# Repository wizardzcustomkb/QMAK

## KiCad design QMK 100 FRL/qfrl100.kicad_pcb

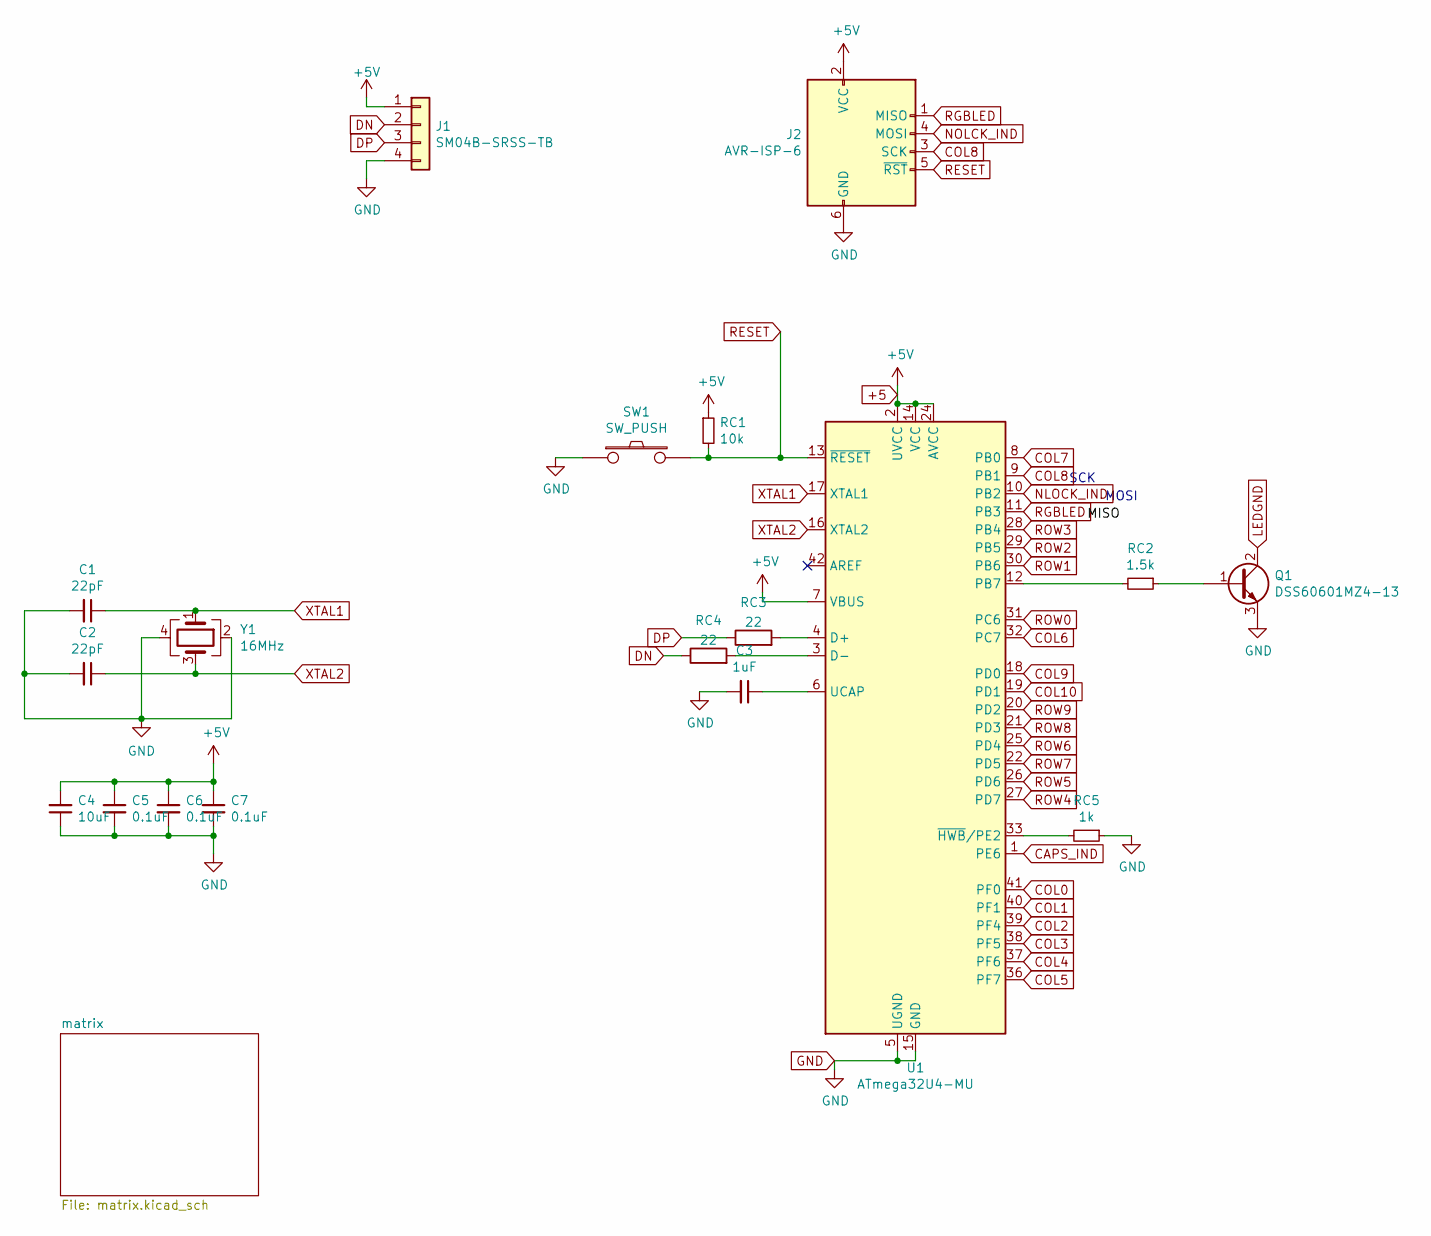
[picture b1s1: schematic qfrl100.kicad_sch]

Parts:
C1, C2: 22pF; C_0603_1608Metric
C3: 1uF; C_0603_1608Metric
C4: 10uF; C_0603_1608Metric
C5, C6, C7: 0.1uF; C_0603_1608Metric
J1: SM04B-SRSS-TB; JST-SR-4
J2: AVR-ISP-6; Reset_Pretty-Mask
Q1: DSS60601MZ4-13; SOT-223-3_TabPin2
RC1: 10k; R_0603_1608Metric
RC2: 1.5k; R_0603_1608Metric
RC3, RC4: 22; R_0603_1608Metric
RC5: 1k; R_0603_1608Metric
SW1: SW_PUSH; SKQG-1155865
U1: ATmega32U4-MU; QFN-44-1EP_7x7mm_P0.5mm_EP5.2x5.2mm
Y1: 16MHz; Crystal_SMD_3225-4Pin_3.2x2.5mm

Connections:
+5: C4.2, C5.1, C6.1, C7.1, J1.1, J2.2 (VCC), RC1.1, U1.2 (UVCC), U1.7 (VBUS), U1.14 (VCC), U1.24 (AVCC), U1.34 (VCC), U1.44 (AVCC)
CAPS_IND: U1.1 (PE6); also elsewhere on the board
COL0: U1.41 (PF0); also elsewhere on the board
COL1: U1.40 (PF1); also elsewhere on the board
COL2: U1.39 (PF4); also elsewhere on the board
COL3: U1.38 (PF5); also elsewhere on the board
COL4: U1.37 (PF6); also elsewhere on the board
COL5: U1.36 (PF7); also elsewhere on the board
COL6: U1.32 (PC7); also elsewhere on the board
COL7: U1.8 (PB0); also elsewhere on the board
COL8: J2.3 (SCK), U1.9 (PB1); also elsewhere on the board
COL9: U1.18 (PD0); also elsewhere on the board
COL10: U1.19 (PD1); also elsewhere on the board
DN: J1.2, RC4.1
DP: J1.3, RC3.1
GND: C1.2, C2.2, C3.2, C4.1, C5.2, C6.2, C7.2, J1.4, J2.6 (GND), Q1.3 (E), RC5.1, SW1.1, U1.5 (UGND), U1.15 (GND), U1.23 (GND), U1.35 (GND), U1.43 (GND), U1.45 (GND), Y1.2, Y1.4
LEDGND: Q1.2 (C); also elsewhere on the board
NLOCK_IND: U1.10 (PB2); also elsewhere on the board
NOLCK_IND: J2.4 (MOSI)
unnamed: C3.1, U1.6 (UCAP)
unnamed: Q1.1 (B), RC2.1
unnamed: RC2.2, U1.12 (PB7)
unnamed: RC3.2, U1.4 (D+)
unnamed: RC4.2, U1.3 (D-)
unnamed: RC5.2, U1.33 (~HWB/PE2)
RESET: J2.5 (~RST), RC1.2, SW1.2, U1.13 (~RESET)
RGBLED: J2.1 (MISO), U1.11 (PB3)
ROW0: U1.31 (PC6); also elsewhere on the board
ROW1: U1.30 (PB6); also elsewhere on the board
ROW2: U1.29 (PB5); also elsewhere on the board
ROW3: U1.28 (PB4); also elsewhere on the board
ROW4: U1.27 (PD7); also elsewhere on the board
ROW5: U1.26 (PD6); also elsewhere on the board
ROW6: U1.25 (PD4); also elsewhere on the board
ROW7: U1.22 (PD5); also elsewhere on the board
ROW8: U1.21 (PD3); also elsewhere on the board
ROW9: U1.20 (PD2); also elsewhere on the board
XTAL1: C1.1, U1.17 (XTAL1), Y1.1
XTAL2: C2.1, U1.16 (XTAL2), Y1.3

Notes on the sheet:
MOSI
SCK

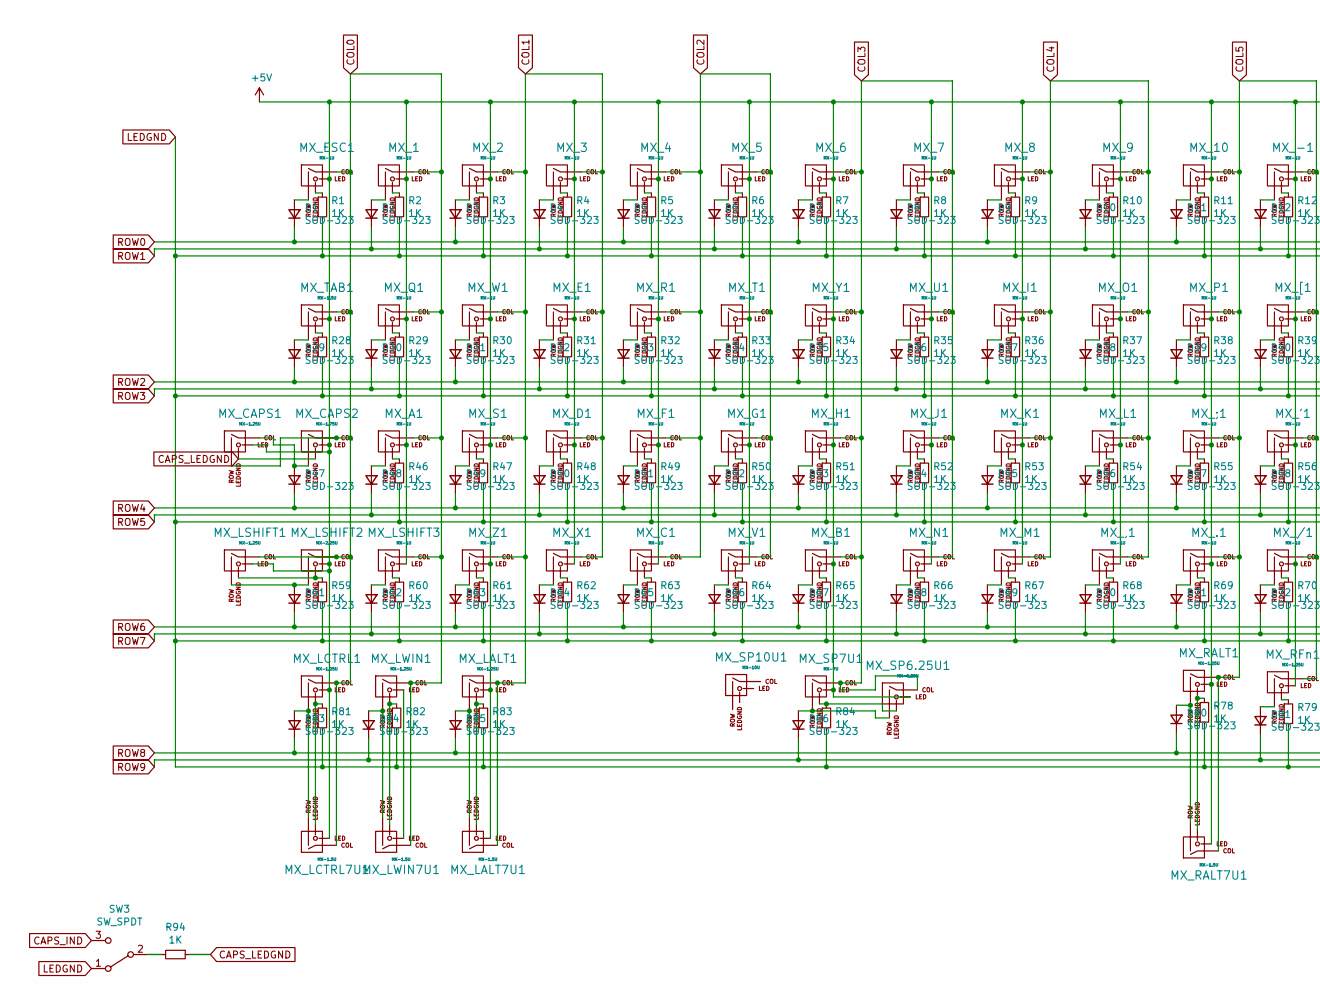
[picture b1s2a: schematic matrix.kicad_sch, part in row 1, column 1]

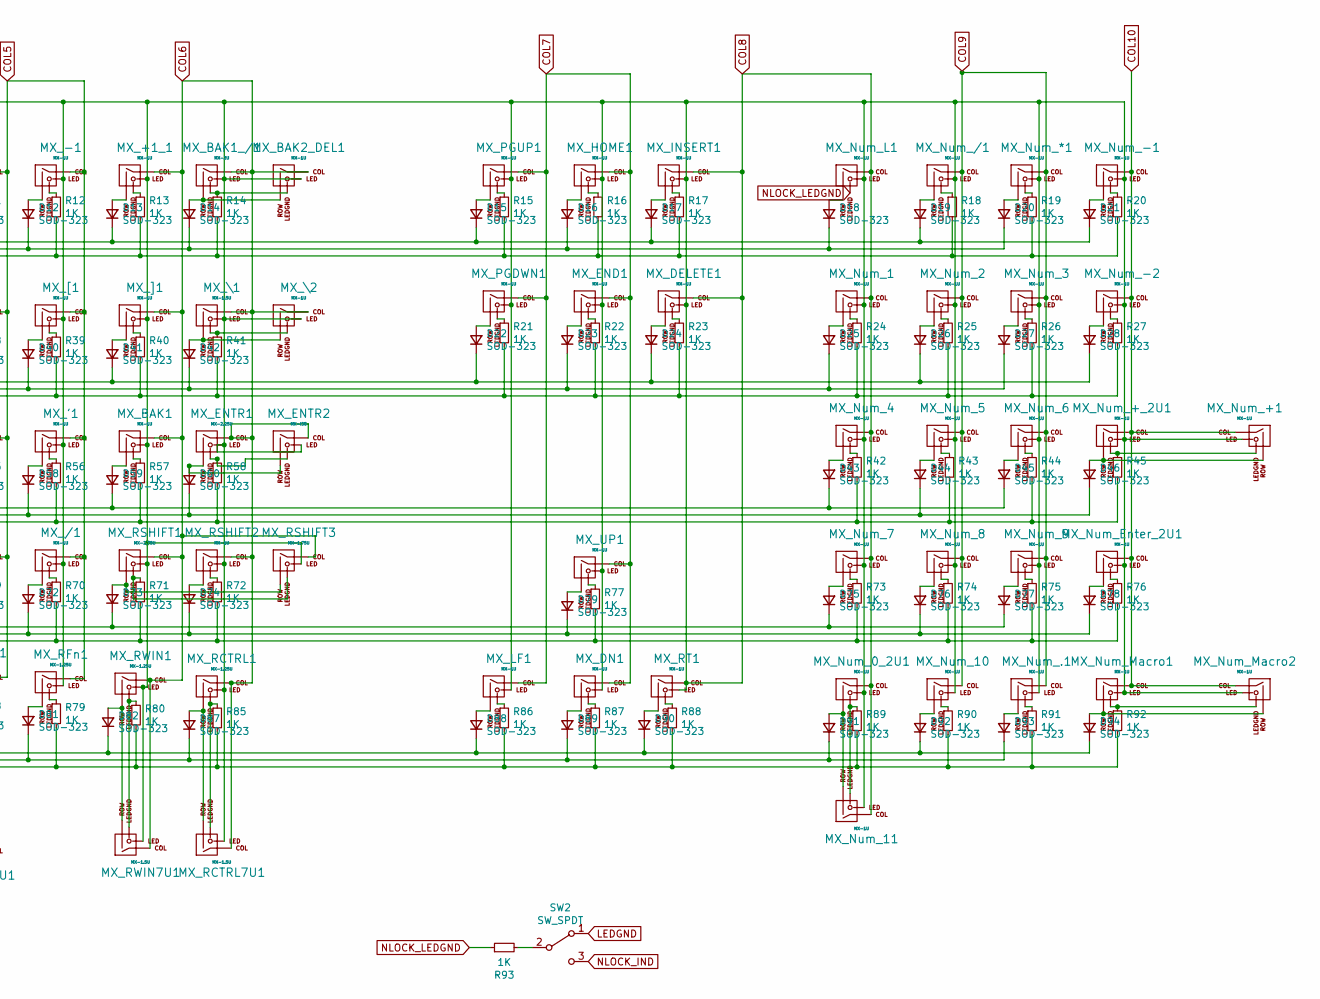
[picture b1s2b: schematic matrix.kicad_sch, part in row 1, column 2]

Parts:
D1, D2, D3, D4, D5, D6, D7, D8, D9, D10, D11, D12, D13, D14, D15, D16, D17, D18, D19, D20, D21, D22, D23, D24, D25, D26, D27, D28, D29, D30, D31, D32, D33, D34, D35, D36, D37, D38, D39, D40, D41, D42, D43, D44, D45, D46, D47, D48, D49, D50, D51, D52, D53, D54, D55, D56, D57, D58, D59, D60, D61, D62, D63, D64, D65, D66, D67, D68, D69, D70, D71, D72, D73, D74, D75, D76, D77, D78, D79, D80, D81, D82, D83, D84, D85, D86, D87, D88, D89, D90, D91, D92, D93, D94: SOD-323; D_SOD-123
MX_1, MX_2, MX_3, MX_4, MX_5, MX_6, MX_7, MX_8, MX_9, MX_10, MX_.1: MX-1U
MX_'1: MX-1U
MX_+1_1: MX-1U
MX_,1: MX-1U
MX_-1: MX-1U
MX_/1: MX-1U
MX_;1: MX-1U
MX_A1: MX-1U
MX_B1: MX-1U
MX_BAK1, MX_BAK2_DEL1: MX-1U
MX_BAK1_/1: MX-2U
MX_C1: MX-1U
MX_CAPS1: MX-1.25U
MX_CAPS2: MX-1.75U
MX_D1: MX-1U
MX_DELETE1: MX-1U
MX_DN1: MX-1U
MX_E1: MX-1U
MX_END1: MX-1U
MX_ENTR1: MX-2.25U; MX-2.25U-ReversedStabilizers
MX_ENTR2: MX-ISO; MX-ISO-FLIPPED-ReversedStabilizers
MX_ESC1: MX-1U
MX_F1: MX-1U
MX_G1: MX-1U
MX_H1: MX-1U
MX_HOME1: MX-1U
MX_I1: MX-1U
MX_INSERT1: MX-1U
MX_J1: MX-1U
MX_K1: MX-1U
MX_L1: MX-1U
MX_LALT1: MX-1.25U
MX_LALT7U1: MX-1.5U
MX_LCTRL1: MX-1.25U
MX_LCTRL7U1: MX-1.5U
MX_LF1: MX-1U
MX_LSHIFT1: MX-1.25U
MX_LSHIFT2: MX-2.25U
MX_LSHIFT3: MX-1U
MX_LWIN1: MX-1.25U
MX_LWIN7U1: MX-1.5U; MX-1U
MX_M1: MX-1U
MX_N1: MX-1U
MX_Num_0_2U1: MX-1U; MX-2U
MX_Num_1, MX_Num_2, MX_Num_3, MX_Num_4, MX_Num_5, MX_Num_6, MX_Num_7, MX_Num_8, MX_Num_9, MX_Num_10, MX_Num_11, MX_Num_.1: MX-1U
MX_Num_*1: MX-1U
MX_Num_+1: MX-1U
MX_Num_+_2U1: MX-1U; MX-2U
MX_Num_-1, MX_Num_-2: MX-1U
MX_Num_/1: MX-1U
MX_Num_Enter_2U1: MX-1U; MX-2U
MX_Num_L1: MX-1U
MX_Num_Macro1, MX_Num_Macro2: MX-1U
MX_O1: MX-1U
MX_P1: MX-1U
MX_PGDWN1: MX-1U
MX_PGUP1: MX-1U
MX_Q1: MX-1U
MX_R1: MX-1U
MX_RALT1: MX-1.25U
MX_RALT7U1: MX-1.5U
MX_RCTRL1: MX-1.25U
MX_RCTRL7U1: MX-1.5U
MX_RFn1: MX-1.25U
MX_RSHIFT1: MX-2.75U
MX_RSHIFT2: MX-1U
MX_RSHIFT3: MX-1.75U
MX_RT1: MX-1U
MX_RWIN1: MX-1.25U
MX_RWIN7U1: MX-1.5U; MX-1U
MX_S1: MX-1U
MX_SP6.25U1: MX-6.25U
MX_SP7U1: MX-7U
MX_SP10U1: MX-10U
MX_T1: MX-1U
MX_TAB1: MX-1.5U
MX_U1: MX-1U
MX_UP1: MX-1U
MX_V1: MX-1U
MX_W1: MX-1U
MX_X1: MX-1U
MX_Y1: MX-1U
MX_Z1: MX-1U
MX_[1: MX-1U
MX_\1: MX-1.5U
MX_\2: MX-1U
MX_]1: MX-1U
R1, R2, R3, R4, R5, R6, R7, R8, R9, R10, R11, R12, R13, R14, R15, R16, R17, R18, R19, R20, R21, R22, R23, R24, R25, R26, R27, R28, R29, R30, R31, R32, R33, R34, R35, R36, R37, R38, R39, R40, R41, R42, R43, R44, R45, R46, R47, R48, R49, R50, R51, R52, R53, R54, R55, R56, R57, R58, R59, R60, R61, R62, R63, R64, R65, R66, R67, R68, R69, R70, R71, R72, R73, R74, R75, R76, R77, R78, R79, R80, R81, R82, R83, R84, R85, R86, R87, R88, R89, R90, R91, R92, R93, R94: 1K; R_0603_1608Metric
SW2, SW3: SW_SPDT; SW_SPDT_PCM12

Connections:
CAPS_IND: SW3.3 (C); also elsewhere on the board
CAPS_LEDGND: MX_CAPS1.4 (LEDGND), MX_CAPS2.4 (LEDGND), R94.1
COL0: MX_1.1 (COL), MX_A1.1 (COL), MX_CAPS1.2 (ROW), MX_CAPS2.1 (COL), MX_ESC1.1 (COL), MX_LCTRL1.1 (COL), MX_LCTRL7U1.1 (COL), MX_LSHIFT1.1 (COL), MX_LSHIFT2.1 (COL), MX_LSHIFT3.1 (COL), MX_LWIN1.1 (COL), MX_LWIN7U1.1 (COL), MX_Q1.1 (COL), MX_TAB1.1 (COL); also elsewhere on the board
COL1: MX_2.1 (COL), MX_3.1 (COL), MX_D1.1 (COL), MX_E1.1 (COL), MX_LALT1.1 (COL), MX_LALT7U1.1 (COL), MX_S1.1 (COL), MX_W1.1 (COL), MX_X1.1 (COL), MX_Z1.1 (COL); also elsewhere on the board
COL2: MX_4.1 (COL), MX_5.1 (COL), MX_C1.1 (COL), MX_F1.1 (COL), MX_G1.1 (COL), MX_R1.1 (COL), MX_T1.1 (COL), MX_V1.1 (COL); also elsewhere on the board
COL3: MX_6.1 (COL), MX_7.1 (COL), MX_B1.1 (COL), MX_H1.1 (COL), MX_J1.1 (COL), MX_N1.1 (COL), MX_SP6.25U1.1 (COL), MX_SP7U1.1 (COL), MX_U1.1 (COL), MX_Y1.1 (COL); also elsewhere on the board
COL4: MX_8.1 (COL), MX_9.1 (COL), MX_,1.1 (COL), MX_I1.1 (COL), MX_K1.1 (COL), MX_L1.1 (COL), MX_M1.1 (COL), MX_O1.1 (COL); also elsewhere on the board
COL5: MX_10.1 (COL), MX_'1.1 (COL), MX_-1.1 (COL), MX_.1.1 (COL), MX_/1.1 (COL), MX_;1.1 (COL), MX_P1.1 (COL), MX_RALT1.1 (COL), MX_RALT7U1.1 (COL), MX_RFn1.1 (COL), MX_[1.1 (COL); also elsewhere on the board
COL6: MX_+1_1.1 (COL), MX_BAK1.1 (COL), MX_BAK1_/1.1 (COL), MX_BAK2_DEL1.1 (COL), MX_ENTR1.1 (COL), MX_ENTR2.1 (COL), MX_RCTRL1.1 (COL), MX_RCTRL7U1.1 (COL), MX_RSHIFT1.1 (COL), MX_RSHIFT2.1 (COL), MX_RSHIFT3.1 (COL), MX_RWIN1.1 (COL), MX_RWIN7U1.1 (COL), MX_\1.1 (COL), MX_\2.1 (COL), MX_]1.1 (COL); also elsewhere on the board
COL7: MX_DN1.1 (COL), MX_END1.1 (COL), MX_HOME1.1 (COL), MX_LF1.1 (COL), MX_PGDWN1.1 (COL), MX_PGUP1.1 (COL), MX_UP1.1 (COL); also elsewhere on the board
COL8: MX_1.3 (LED), MX_2.3 (LED), MX_3.3 (LED), MX_4.3 (LED), MX_5.3 (LED), MX_6.3 (LED), MX_7.3 (LED), MX_8.3 (LED), MX_9.3 (LED), MX_10.3 (LED), MX_'1.3 (LED), MX_+1_1.3 (LED), MX_,1.3 (LED), MX_-1.3 (LED), MX_.1.3 (LED), MX_/1.3 (LED), MX_;1.3 (LED), MX_A1.3 (LED), MX_B1.3 (LED), MX_BAK1.3 (LED), MX_BAK1_/1.3 (LED), MX_BAK2_DEL1.3 (LED), MX_C1.3 (LED), MX_CAPS1.3 (LED), MX_CAPS2.3 (LED), MX_D1.3 (LED), MX_DELETE1.1 (COL), MX_DELETE1.3 (LED), MX_DN1.3 (LED), MX_E1.3 (LED), MX_END1.3 (LED), MX_ENTR1.3 (LED), MX_ENTR2.3 (LED), MX_ESC1.3 (LED), MX_F1.3 (LED), MX_G1.3 (LED), MX_H1.3 (LED), MX_HOME1.3 (LED), MX_I1.3 (LED), MX_INSERT1.1 (COL), MX_INSERT1.3 (LED), MX_J1.3 (LED), MX_K1.3 (LED), MX_L1.3 (LED), MX_LALT1.3 (LED), MX_LALT7U1.3 (LED), MX_LCTRL1.3 (LED), MX_LCTRL7U1.3 (LED), MX_LF1.3 (LED), MX_LSHIFT1.3 (LED), MX_LSHIFT2.3 (LED), MX_LSHIFT3.3 (LED), MX_M1.3 (LED), MX_N1.3 (LED), MX_Num_0_2U1.1 (COL), MX_Num_0_2U1.3 (LED), MX_Num_1.1 (COL), MX_Num_1.3 (LED), MX_Num_2.3 (LED), MX_Num_3.3 (LED), MX_Num_4.1 (COL), MX_Num_4.3 (LED), MX_Num_5.3 (LED), MX_Num_6.3 (LED), MX_Num_7.1 (COL), MX_Num_7.3 (LED), MX_Num_8.3 (LED), MX_Num_9.3 (LED), MX_Num_10.3 (LED), MX_Num_11.1 (COL), MX_Num_11.3 (LED), MX_Num_*1.3 (LED), MX_Num_+1.3 (LED), MX_Num_+_2U1.3 (LED), MX_Num_-1.3 (LED), MX_Num_-2.3 (LED), MX_Num_.1.3 (LED), MX_Num_/1.3 (LED), MX_Num_Enter_2U1.3 (LED), MX_Num_L1.1 (COL), MX_Num_L1.3 (LED), MX_Num_Macro1.3 (LED), MX_Num_Macro2.3 (LED), MX_O1.3 (LED), MX_P1.3 (LED), MX_PGDWN1.3 (LED), MX_PGUP1.3 (LED), MX_Q1.3 (LED), MX_R1.3 (LED), MX_RALT1.3 (LED), MX_RALT7U1.3 (LED), MX_RCTRL1.3 (LED), MX_RCTRL7U1.3 (LED), MX_RFn1.3 (LED), MX_RSHIFT1.3 (LED), MX_RSHIFT2.3 (LED), MX_RSHIFT3.3 (LED), MX_RT1.1 (COL), MX_RT1.3 (LED), MX_RWIN1.3 (LED), MX_RWIN7U1.3 (LED), MX_S1.3 (LED), MX_SP6.25U1.3 (LED), MX_SP7U1.3 (LED), MX_T1.3 (LED), MX_TAB1.3 (LED), MX_U1.3 (LED), MX_UP1.3 (LED), MX_V1.3 (LED), MX_W1.3 (LED), MX_X1.3 (LED), MX_Y1.3 (LED), MX_Z1.3 (LED), MX_[1.3 (LED), MX_\1.3 (LED), MX_\2.3 (LED), MX_]1.3 (LED); also elsewhere on the board
COL9: MX_Num_2.1 (COL), MX_Num_3.1 (COL), MX_Num_5.1 (COL), MX_Num_6.1 (COL), MX_Num_8.1 (COL), MX_Num_9.1 (COL), MX_Num_10.1 (COL), MX_Num_*1.1 (COL), MX_Num_.1.1 (COL), MX_Num_/1.1 (COL); also elsewhere on the board
COL10: MX_Num_+1.1 (COL), MX_Num_+_2U1.1 (COL), MX_Num_-1.1 (COL), MX_Num_-2.1 (COL), MX_Num_Enter_2U1.1 (COL), MX_Num_Macro1.1 (COL), MX_Num_Macro2.1 (COL); also elsewhere on the board
LEDGND: R1.2, R2.2, R3.2, R4.2, R5.2, R6.2, R7.2, R8.2, R9.2, R10.2, R11.2, R12.2, R13.2, R14.2, R15.2, R16.2, R17.2, R18.2, R19.2, R20.2, R21.2, R22.2, R23.2, R24.2, R25.2, R26.2, R27.2, R28.2, R29.2, R30.2, R31.2, R32.2, R33.2, R34.2, R35.2, R36.2, R37.2, R38.2, R39.2, R40.2, R41.2, R42.2, R43.2, R44.2, R45.2, R46.2, R47.2, R48.2, R49.2, R50.2, R51.2, R52.2, R53.2, R54.2, R55.2, R56.2, R57.2, R58.2, R59.2, R60.2, R61.2, R62.2, R63.2, R64.2, R65.2, R66.2, R67.2, R68.2, R69.2, R70.2, R71.2, R72.2, R73.2, R74.2, R75.2, R76.2, R77.2, R78.2, R79.2, R80.2, R81.2, R82.2, R83.2, R84.2, R85.2, R86.2, R87.2, R88.2, R89.2, R90.2, R91.2, R92.2, SW2.1 (A), SW3.1 (A); also elsewhere on the board
NLOCK_IND: SW2.3 (C); also elsewhere on the board
NLOCK_LEDGND: MX_Num_L1.4 (LEDGND), R93.1
unnamed: D1.2 (A), MX_ESC1.2 (ROW)
unnamed: D2.2 (A), MX_1.2 (ROW)
unnamed: D3.2 (A), MX_2.2 (ROW)
unnamed: D4.2 (A), MX_3.2 (ROW)
unnamed: D5.2 (A), MX_4.2 (ROW)
unnamed: D6.2 (A), MX_5.2 (ROW)
unnamed: D7.2 (A), MX_6.2 (ROW)
unnamed: D8.2 (A), MX_7.2 (ROW)
unnamed: D9.2 (A), MX_8.2 (ROW)
unnamed: D10.2 (A), MX_9.2 (ROW)
unnamed: D11.2 (A), MX_10.2 (ROW)
unnamed: D12.2 (A), MX_-1.2 (ROW)
unnamed: D13.2 (A), MX_+1_1.2 (ROW)
unnamed: D14.2 (A), MX_BAK1_/1.2 (ROW), MX_BAK2_DEL1.2 (ROW)
unnamed: D15.2 (A), MX_PGUP1.2 (ROW)
unnamed: D16.2 (A), MX_HOME1.2 (ROW)
unnamed: D17.2 (A), MX_INSERT1.2 (ROW)
unnamed: D18.2 (A), MX_Num_L1.2 (ROW)
unnamed: D19.2 (A), MX_Num_/1.2 (ROW)
unnamed: D20.2 (A), MX_Num_*1.2 (ROW)
unnamed: D21.2 (A), MX_Num_-1.2 (ROW)
unnamed: D22.2 (A), MX_PGDWN1.2 (ROW)
unnamed: D23.2 (A), MX_END1.2 (ROW)
unnamed: D24.2 (A), MX_DELETE1.2 (ROW)
unnamed: D25.2 (A), MX_Num_1.2 (ROW)
unnamed: D26.2 (A), MX_Num_2.2 (ROW)
unnamed: D27.2 (A), MX_Num_3.2 (ROW)
unnamed: D28.2 (A), MX_Num_-2.2 (ROW)
unnamed: D29.2 (A), MX_TAB1.2 (ROW)
unnamed: D30.2 (A), MX_Q1.2 (ROW)
unnamed: D31.2 (A), MX_W1.2 (ROW)
unnamed: D32.2 (A), MX_E1.2 (ROW)
unnamed: D33.2 (A), MX_R1.2 (ROW)
unnamed: D34.2 (A), MX_T1.2 (ROW)
unnamed: D35.2 (A), MX_Y1.2 (ROW)
unnamed: D36.2 (A), MX_U1.2 (ROW)
unnamed: D37.2 (A), MX_I1.2 (ROW)
unnamed: D38.2 (A), MX_O1.2 (ROW)
unnamed: D39.2 (A), MX_P1.2 (ROW)
unnamed: D40.2 (A), MX_[1.2 (ROW)
unnamed: D41.2 (A), MX_]1.2 (ROW)
unnamed: D42.2 (A), MX_\1.2 (ROW), MX_\2.2 (ROW)
unnamed: D43.2 (A), MX_Num_4.2 (ROW)
unnamed: D44.2 (A), MX_Num_5.2 (ROW)
unnamed: D45.2 (A), MX_Num_6.2 (ROW)
unnamed: D46.2 (A), MX_Num_+1.2 (ROW), MX_Num_+_2U1.2 (ROW)
unnamed: D47.2 (A), MX_CAPS1.1 (COL), MX_CAPS2.2 (ROW)
unnamed: D48.2 (A), MX_A1.2 (ROW)
unnamed: D49.2 (A), MX_S1.2 (ROW)
unnamed: D50.2 (A), MX_D1.2 (ROW)
unnamed: D51.2 (A), MX_F1.2 (ROW)
unnamed: D52.2 (A), MX_G1.2 (ROW)
unnamed: D53.2 (A), MX_H1.2 (ROW)
unnamed: D54.2 (A), MX_J1.2 (ROW)
unnamed: D55.2 (A), MX_K1.2 (ROW)
unnamed: D56.2 (A), MX_L1.2 (ROW)
unnamed: D57.2 (A), MX_;1.2 (ROW)
unnamed: D58.2 (A), MX_'1.2 (ROW)
unnamed: D59.2 (A), MX_BAK1.2 (ROW)
unnamed: D60.2 (A), MX_ENTR1.2 (ROW), MX_ENTR2.2 (ROW)
unnamed: D61.2 (A), MX_LSHIFT1.2 (ROW), MX_LSHIFT2.2 (ROW)
unnamed: D62.2 (A), MX_LSHIFT3.2 (ROW)
unnamed: D63.2 (A), MX_Z1.2 (ROW)
unnamed: D64.2 (A), MX_X1.2 (ROW)
unnamed: D65.2 (A), MX_C1.2 (ROW)
unnamed: D66.2 (A), MX_V1.2 (ROW)
unnamed: D67.2 (A), MX_B1.2 (ROW)
unnamed: D68.2 (A), MX_N1.2 (ROW)
unnamed: D69.2 (A), MX_M1.2 (ROW)
unnamed: D70.2 (A), MX_,1.2 (ROW)
unnamed: D71.2 (A), MX_.1.2 (ROW)
unnamed: D72.2 (A), MX_/1.2 (ROW)
unnamed: D73.2 (A), MX_RSHIFT1.2 (ROW), MX_RSHIFT3.2 (ROW)
unnamed: D74.2 (A), MX_RSHIFT2.2 (ROW)
unnamed: D75.2 (A), MX_Num_7.2 (ROW)
unnamed: D76.2 (A), MX_Num_8.2 (ROW)
unnamed: D77.2 (A), MX_Num_9.2 (ROW)
unnamed: D78.2 (A), MX_Num_Enter_2U1.2 (ROW)
unnamed: D79.2 (A), MX_UP1.2 (ROW)
unnamed: D80.2 (A), MX_RALT1.2 (ROW), MX_RALT7U1.2 (ROW)
unnamed: D81.2 (A), MX_RFn1.2 (ROW)
unnamed: D82.2 (A), MX_RWIN1.2 (ROW), MX_RWIN7U1.2 (ROW)
unnamed: D83.2 (A), MX_LCTRL1.2 (ROW), MX_LCTRL7U1.2 (ROW)
unnamed: D84.2 (A), MX_LWIN1.2 (ROW), MX_LWIN7U1.2 (ROW)
unnamed: D85.2 (A), MX_LALT1.2 (ROW), MX_LALT7U1.2 (ROW)
unnamed: D86.2 (A), MX_SP6.25U1.2 (ROW), MX_SP7U1.2 (ROW)
unnamed: D87.2 (A), MX_RCTRL1.2 (ROW), MX_RCTRL7U1.2 (ROW)
unnamed: D88.2 (A), MX_LF1.2 (ROW)
unnamed: D89.2 (A), MX_DN1.2 (ROW)
unnamed: D90.2 (A), MX_RT1.2 (ROW)
unnamed: D91.2 (A), MX_Num_0_2U1.2 (ROW), MX_Num_11.2 (ROW)
unnamed: D92.2 (A), MX_Num_10.2 (ROW)
unnamed: D93.2 (A), MX_Num_.1.2 (ROW)
unnamed: D94.2 (A), MX_Num_Macro1.2 (ROW), MX_Num_Macro2.2 (ROW)
unnamed: MX_1.4 (LEDGND), R2.1
unnamed: MX_2.4 (LEDGND), R3.1
unnamed: MX_3.4 (LEDGND), R4.1
unnamed: MX_4.4 (LEDGND), R5.1
unnamed: MX_5.4 (LEDGND), R6.1
unnamed: MX_6.4 (LEDGND), R7.1
unnamed: MX_7.4 (LEDGND), R8.1
unnamed: MX_8.4 (LEDGND), R9.1
unnamed: MX_9.4 (LEDGND), R10.1
unnamed: MX_10.4 (LEDGND), R11.1
unnamed: MX_'1.4 (LEDGND), R56.1
unnamed: MX_+1_1.4 (LEDGND), R13.1
unnamed: MX_,1.4 (LEDGND), R68.1
unnamed: MX_-1.4 (LEDGND), R12.1
unnamed: MX_.1.4 (LEDGND), R69.1
unnamed: MX_/1.4 (LEDGND), R70.1
unnamed: MX_;1.4 (LEDGND), R55.1
unnamed: MX_A1.4 (LEDGND), R46.1
unnamed: MX_B1.4 (LEDGND), R65.1
unnamed: MX_BAK1.4 (LEDGND), R57.1
unnamed: MX_BAK1_/1.4 (LEDGND), MX_BAK2_DEL1.4 (LEDGND), R14.1
unnamed: MX_C1.4 (LEDGND), R63.1
unnamed: MX_D1.4 (LEDGND), R48.1
unnamed: MX_DELETE1.4 (LEDGND), R23.1
unnamed: MX_DN1.4 (LEDGND), R87.1
unnamed: MX_E1.4 (LEDGND), R31.1
unnamed: MX_END1.4 (LEDGND), R22.1
unnamed: MX_ENTR1.4 (LEDGND), MX_ENTR2.4 (LEDGND), R58.1
unnamed: MX_ESC1.4 (LEDGND), R1.1
unnamed: MX_F1.4 (LEDGND), R49.1
unnamed: MX_G1.4 (LEDGND), R50.1
unnamed: MX_H1.4 (LEDGND), R51.1
unnamed: MX_HOME1.4 (LEDGND), R16.1
unnamed: MX_I1.4 (LEDGND), R36.1
unnamed: MX_INSERT1.4 (LEDGND), R17.1
unnamed: MX_J1.4 (LEDGND), R52.1
unnamed: MX_K1.4 (LEDGND), R53.1
unnamed: MX_L1.4 (LEDGND), R54.1
unnamed: MX_LALT1.4 (LEDGND), MX_LALT7U1.4 (LEDGND), R83.1
unnamed: MX_LCTRL1.4 (LEDGND), MX_LCTRL7U1.4 (LEDGND), R81.1
unnamed: MX_LF1.4 (LEDGND), R86.1
unnamed: MX_LSHIFT1.4 (LEDGND), MX_LSHIFT2.4 (LEDGND), R59.1
unnamed: MX_LSHIFT3.4 (LEDGND), R60.1
unnamed: MX_LWIN1.3 (LED), MX_LWIN7U1.3 (LED)
unnamed: MX_LWIN1.4 (LEDGND), MX_LWIN7U1.4 (LEDGND), R82.1
unnamed: MX_M1.4 (LEDGND), R67.1
unnamed: MX_N1.4 (LEDGND), R66.1
unnamed: MX_Num_0_2U1.4 (LEDGND), MX_Num_11.4 (LEDGND), R89.1
unnamed: MX_Num_1.4 (LEDGND), R24.1
unnamed: MX_Num_2.4 (LEDGND), R25.1
unnamed: MX_Num_3.4 (LEDGND), R26.1
unnamed: MX_Num_4.4 (LEDGND), R42.1
unnamed: MX_Num_5.4 (LEDGND), R43.1
unnamed: MX_Num_6.4 (LEDGND), R44.1
unnamed: MX_Num_7.4 (LEDGND), R73.1
unnamed: MX_Num_8.4 (LEDGND), R74.1
unnamed: MX_Num_9.4 (LEDGND), R75.1
unnamed: MX_Num_10.4 (LEDGND), R90.1
unnamed: MX_Num_*1.4 (LEDGND), R19.1
unnamed: MX_Num_+1.4 (LEDGND), MX_Num_+_2U1.4 (LEDGND), R45.1
unnamed: MX_Num_-1.4 (LEDGND), R20.1
unnamed: MX_Num_-2.4 (LEDGND), R27.1
unnamed: MX_Num_.1.4 (LEDGND), R91.1
unnamed: MX_Num_/1.4 (LEDGND), R18.1
unnamed: MX_Num_Enter_2U1.4 (LEDGND), R76.1
unnamed: MX_Num_Macro1.4 (LEDGND), MX_Num_Macro2.4 (LEDGND), R92.1
unnamed: MX_O1.4 (LEDGND), R37.1
unnamed: MX_P1.4 (LEDGND), R38.1
unnamed: MX_PGDWN1.4 (LEDGND), R21.1
unnamed: MX_PGUP1.4 (LEDGND), R15.1
unnamed: MX_Q1.4 (LEDGND), R29.1
unnamed: MX_R1.4 (LEDGND), R32.1
unnamed: MX_RALT1.4 (LEDGND), MX_RALT7U1.4 (LEDGND), R78.1
unnamed: MX_RCTRL1.4 (LEDGND), MX_RCTRL7U1.4 (LEDGND), R85.1
unnamed: MX_RFn1.4 (LEDGND), R79.1
unnamed: MX_RSHIFT1.4 (LEDGND), MX_RSHIFT3.4 (LEDGND), R71.1
unnamed: MX_RSHIFT2.4 (LEDGND), R72.1
unnamed: MX_RT1.4 (LEDGND), R88.1
unnamed: MX_RWIN1.4 (LEDGND), MX_RWIN7U1.4 (LEDGND), R80.1
unnamed: MX_S1.4 (LEDGND), R47.1
unnamed: MX_SP6.25U1.4 (LEDGND), MX_SP7U1.4 (LEDGND), R84.1
unnamed: MX_T1.4 (LEDGND), R33.1
unnamed: MX_TAB1.4 (LEDGND), R28.1
unnamed: MX_U1.4 (LEDGND), R35.1
unnamed: MX_UP1.4 (LEDGND), R77.1
unnamed: MX_V1.4 (LEDGND), R64.1
unnamed: MX_W1.4 (LEDGND), R30.1
unnamed: MX_X1.4 (LEDGND), R62.1
unnamed: MX_Y1.4 (LEDGND), R34.1
unnamed: MX_Z1.4 (LEDGND), R61.1
unnamed: MX_[1.4 (LEDGND), R39.1
unnamed: MX_\1.4 (LEDGND), MX_\2.4 (LEDGND), R41.1
unnamed: MX_]1.4 (LEDGND), R40.1
unnamed: R93.2, SW2.2 (B)
unnamed: R94.2, SW3.2 (B)
ROW0: D1.1 (K), D3.1 (K), D5.1 (K), D7.1 (K), D9.1 (K), D11.1 (K), D13.1 (K), D15.1 (K), D17.1 (K), D19.1 (K), D21.1 (K); also elsewhere on the board
ROW1: D2.1 (K), D4.1 (K), D6.1 (K), D8.1 (K), D10.1 (K), D12.1 (K), D14.1 (K), D16.1 (K), D18.1 (K), D20.1 (K); also elsewhere on the board
ROW2: D22.1 (K), D24.1 (K), D26.1 (K), D28.1 (K), D29.1 (K), D31.1 (K), D33.1 (K), D35.1 (K), D37.1 (K), D39.1 (K), D41.1 (K); also elsewhere on the board
ROW3: D23.1 (K), D25.1 (K), D27.1 (K), D30.1 (K), D32.1 (K), D34.1 (K), D36.1 (K), D38.1 (K), D40.1 (K), D42.1 (K); also elsewhere on the board
ROW4: D43.1 (K), D45.1 (K), D47.1 (K), D49.1 (K), D51.1 (K), D53.1 (K), D55.1 (K), D57.1 (K), D59.1 (K); also elsewhere on the board
ROW5: D44.1 (K), D46.1 (K), D48.1 (K), D50.1 (K), D52.1 (K), D54.1 (K), D56.1 (K), D58.1 (K), D60.1 (K); also elsewhere on the board
ROW6: D61.1 (K), D63.1 (K), D65.1 (K), D67.1 (K), D69.1 (K), D71.1 (K), D73.1 (K), D75.1 (K), D77.1 (K); also elsewhere on the board
ROW7: D62.1 (K), D64.1 (K), D66.1 (K), D68.1 (K), D70.1 (K), D72.1 (K), D74.1 (K), D76.1 (K), D78.1 (K), D79.1 (K); also elsewhere on the board
ROW8: D80.1 (K), D82.1 (K), D83.1 (K), D85.1 (K), D88.1 (K), D90.1 (K), D92.1 (K), D94.1 (K); also elsewhere on the board
ROW9: D81.1 (K), D84.1 (K), D86.1 (K), D87.1 (K), D89.1 (K), D91.1 (K), D93.1 (K); also elsewhere on the board

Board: 2 copper layers, 319 parts (208 on the bottom side), 229 nets, no tracks yet.

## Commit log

2022-10-27 Create QMAK 100 FRL.dxf
    added plate file to the repo
2022-11-29 Create TheFly_DaughterBoard_R1.stp
    added new daughter board
2022-12-10 New pcb project
    created new pcb project for my frl 100 keyboard.
2022-12-15 Working on schema
    Created new mcu schema for the keyboard and added matrix to the drawings
2022-12-16 Changed MCU
    Changed MCU from ATMEL AT90USB1286-AUR to ATMEGA128A-AU which is the newest version.
2022-12-16 working on schematice
    adding new items to the pcb using STM32F072CBT6 MCU and resources
2022-12-17 Added new acheron library and foot prints
    added new files and changed the mcu from STM32F072RBTx to STM32F072R8Tx.
2022-12-23 Updated the pcb schema
    Updated the pcb with a new schema as i am still studying\developing a new pcb for qmak board.
2022-12-23 Added new files to project
    The old project has been scrapped and created a new project using atmega chip instead of stm32 chip. in the future there might be a new pcb version but for the time being this will use atemaga chip f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
2022-12-24 Finished from the first schema and pcb
    Finished the schematics and foot prints links and updated the pcb foot prints to the pcb.
2022-12-29 Updating pcb and schema
    Schema: Fixed some of the schema issues in addition the matrix names require cleaning.
    PCB: Switches has been aligned with the plate to make sure it have proper spacings.
2022-12-30 Updating PCB
    Added first row diodes and resistors to the pcb.
    Note: there might be some clean up if there is no good tracing for diodes.
2023-01-03 Updating pcb
    PCB diodes and resistor has been positioned near switch.
    Next will be mcu and its components then tracing.
2023-01-05 Pcb update
    Repositioned the remain components for the first design.
